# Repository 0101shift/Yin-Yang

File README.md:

# Yin-Yang
Yin-Yang is an e-Badge design inspired from Yin-Yang symbol. The Badge embeds Attiny45 Micro-controller to control NeoPixel LEDs (reverse mounted). The whole badge is powered by a 3V coin cell which is then boosted to 5V by on board Boost circuit to power the badge.

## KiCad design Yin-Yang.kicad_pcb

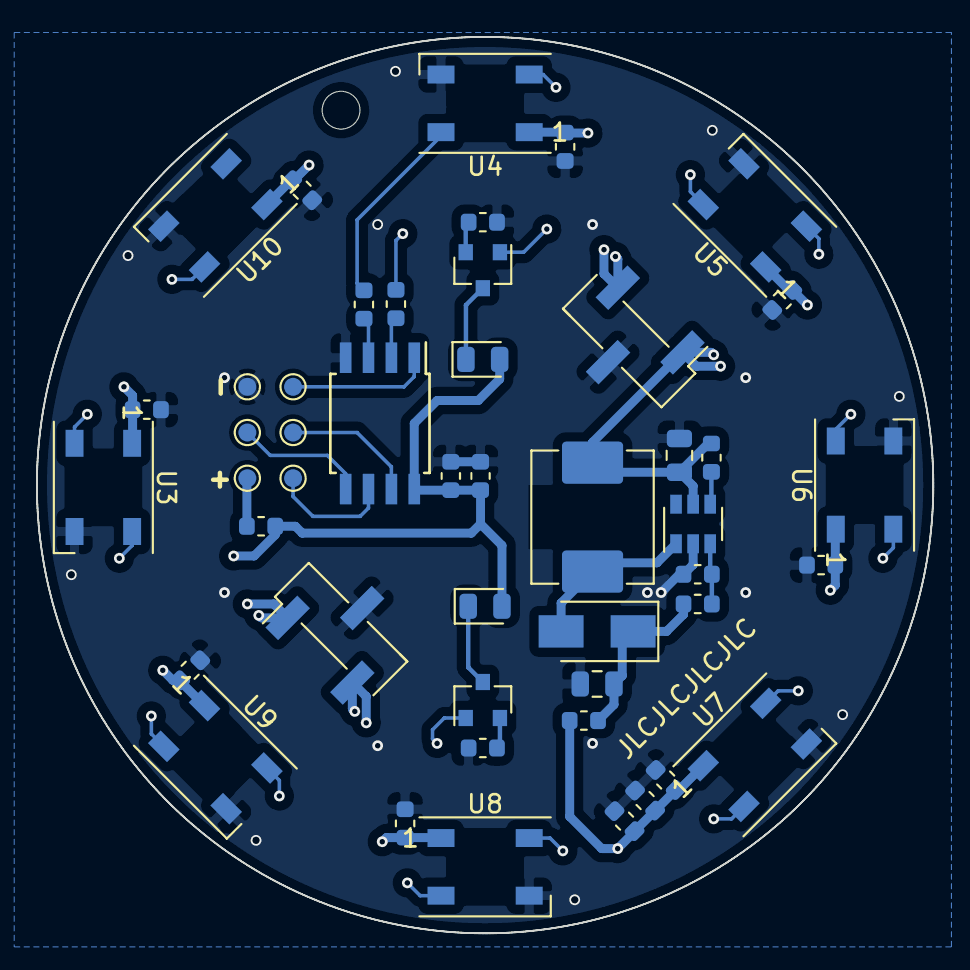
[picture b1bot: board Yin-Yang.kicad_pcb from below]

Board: 4 copper layers, 49.8 x 49.8 mm, 48 parts (47 on the bottom side), 27 nets.

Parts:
C1, C7: 22uF; C_0805_2012Metric
C2, C6: 4.7uF; C_0603_1608Metric
C3, C5, C8, C9, C10, C11, C12, C13, C14: 0.1uF; C_0603_1608Metric
C4: 10uF; C_0603_1608Metric
D1, D3: LED; LED_0805_2012Metric
D2: SS34; D_SMA
J1, J2: Conn_01x03_Male; PinHeader_1x03_P2.54mm_Vertical_SMD_Pin1Left
L1: 22uH; L_Abracon_ASPI-0630LR
Q1, Q2: BC847; SOT-23
R1, R3: 10K; R_0603_1608Metric
R2: 73.33K; R_0603_1608Metric
R4, R5, R6, R7: 0E; R_0603_1608Metric
R8, R9: 560E; R_0603_1608Metric
Ref**: Val**; Yin-Yang_battery_connect
TP1, TP2, TP3, TP4, TP5, TP6: TestPoint; TestPoint_Pad_D1.0mm
U1: MT3608; SOT-23-6
U2: ATtiny85-20SU; SOIJ-8_5.3x5.3mm_P1.27mm
U3, U4, U5, U6, U7, U8, U9, U10: WS2812B_Reverse_Mount; LED_WS2812B_PLCC4_5.0x5.0mm_P3.2mm

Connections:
/Batt: C1.1, J1.1, J1.3, J2.1, J2.3, L1.1, R1.1, U1.5
/LED_OUT: R4.1, U4.4
/LED_OUT1: Q1.1, Q2.1, R5.1
/MISO: TP2.1, U2.6
/MOSI: TP3.1, U2.5
/SCK: TP4.1, U2.7
/Vin: C2.1, C3.1, C4.1, C5.1, C6.1, C8.1, C9.1, C10.1, C11.1, C12.1, C13.1, C14.1, D1.2, D3.2, R6.2, R7.1, U2.8, U3.1, U4.1, U5.1, U6.1, U7.1, U8.1, U9.1, U10.1
/rst: TP1.1, U2.1
GND: C1.2, C2.2, C3.2, C4.2, C5.2, C6.2, C7.2, C8.2, C9.2, C10.2, C11.2, C12.2, C13.2, C14.2, J1.2, J2.2, R3.1, R8.2, R9.2, TP6.1, U1.2, U2.4, U3.3, U4.3, U5.3, U6.3, U7.3, U8.3, U9.3, U10.3
unnamed: C7.1, D2.1, R2.2, R7.2
unnamed: D1.1, Q1.3
unnamed: D2.2, L1.2, U1.1
unnamed: D3.1, Q2.3
unnamed: Q1.2, R8.1
unnamed: Q2.2, R9.1
unnamed: R1.2, U1.4
unnamed: R2.1, R3.2, U1.3
unnamed: R4.2, U2.3
unnamed: R5.2, U2.2
unnamed: R6.1, TP5.1
unnamed: U3.4, U9.2
unnamed: U4.2, U5.4
unnamed: U5.2, U6.4
unnamed: U6.2, U7.4
unnamed: U7.2, U8.4
unnamed: U8.2, U9.4
unnamed: U3.2, U10.4

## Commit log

2022-06-18 Add files via upload
    Added Project Design files
2022-06-18 Update README.md
    Added Images
2022-06-20 Add files via upload
    Added Design in .pdf format
